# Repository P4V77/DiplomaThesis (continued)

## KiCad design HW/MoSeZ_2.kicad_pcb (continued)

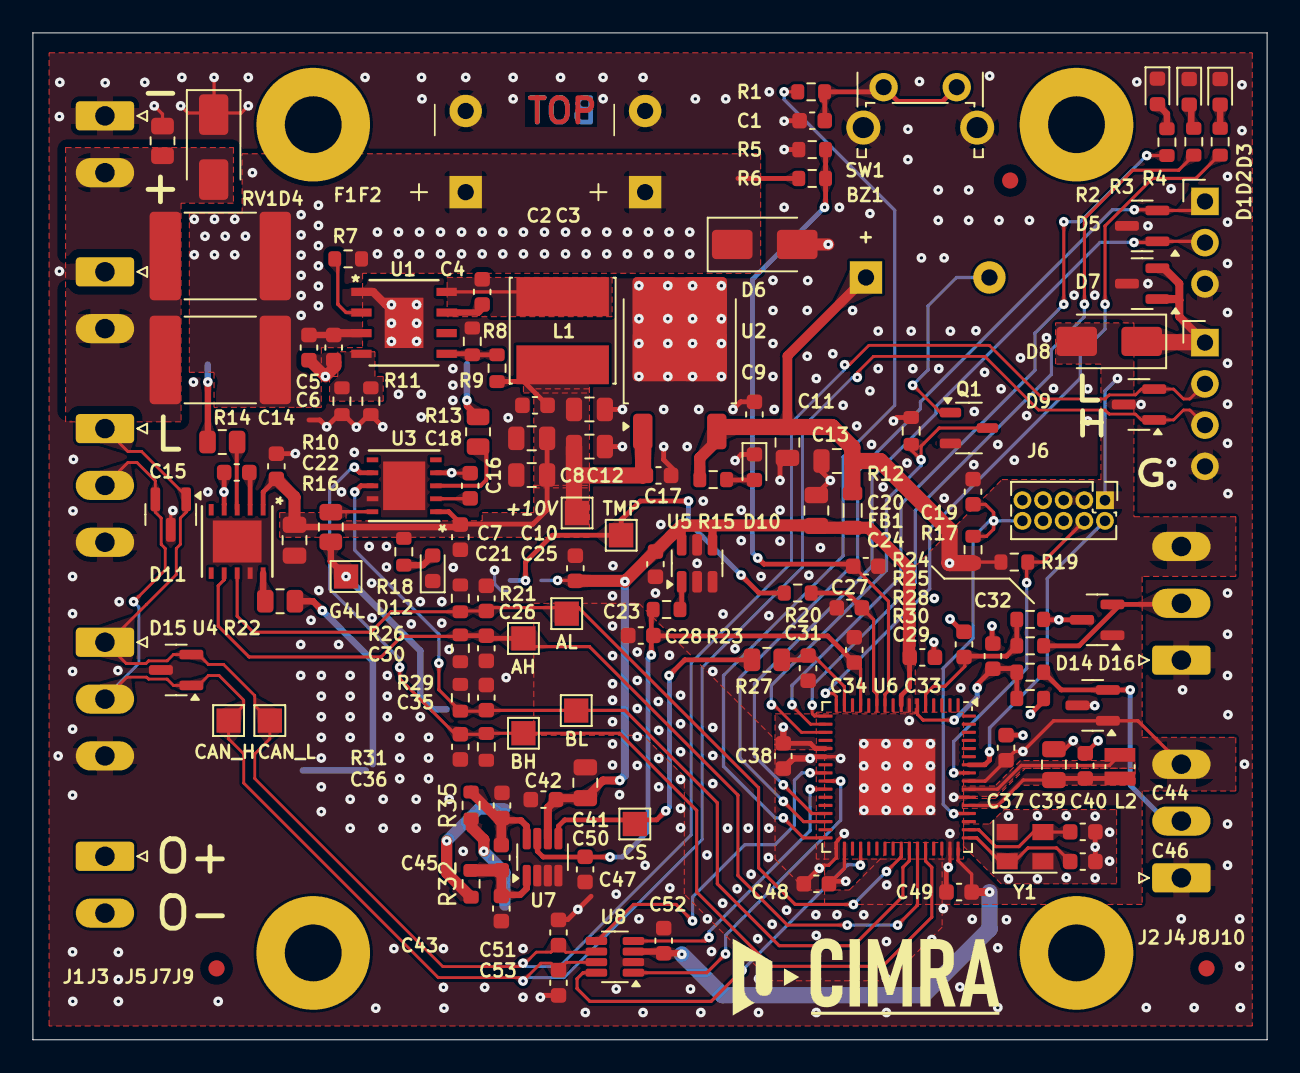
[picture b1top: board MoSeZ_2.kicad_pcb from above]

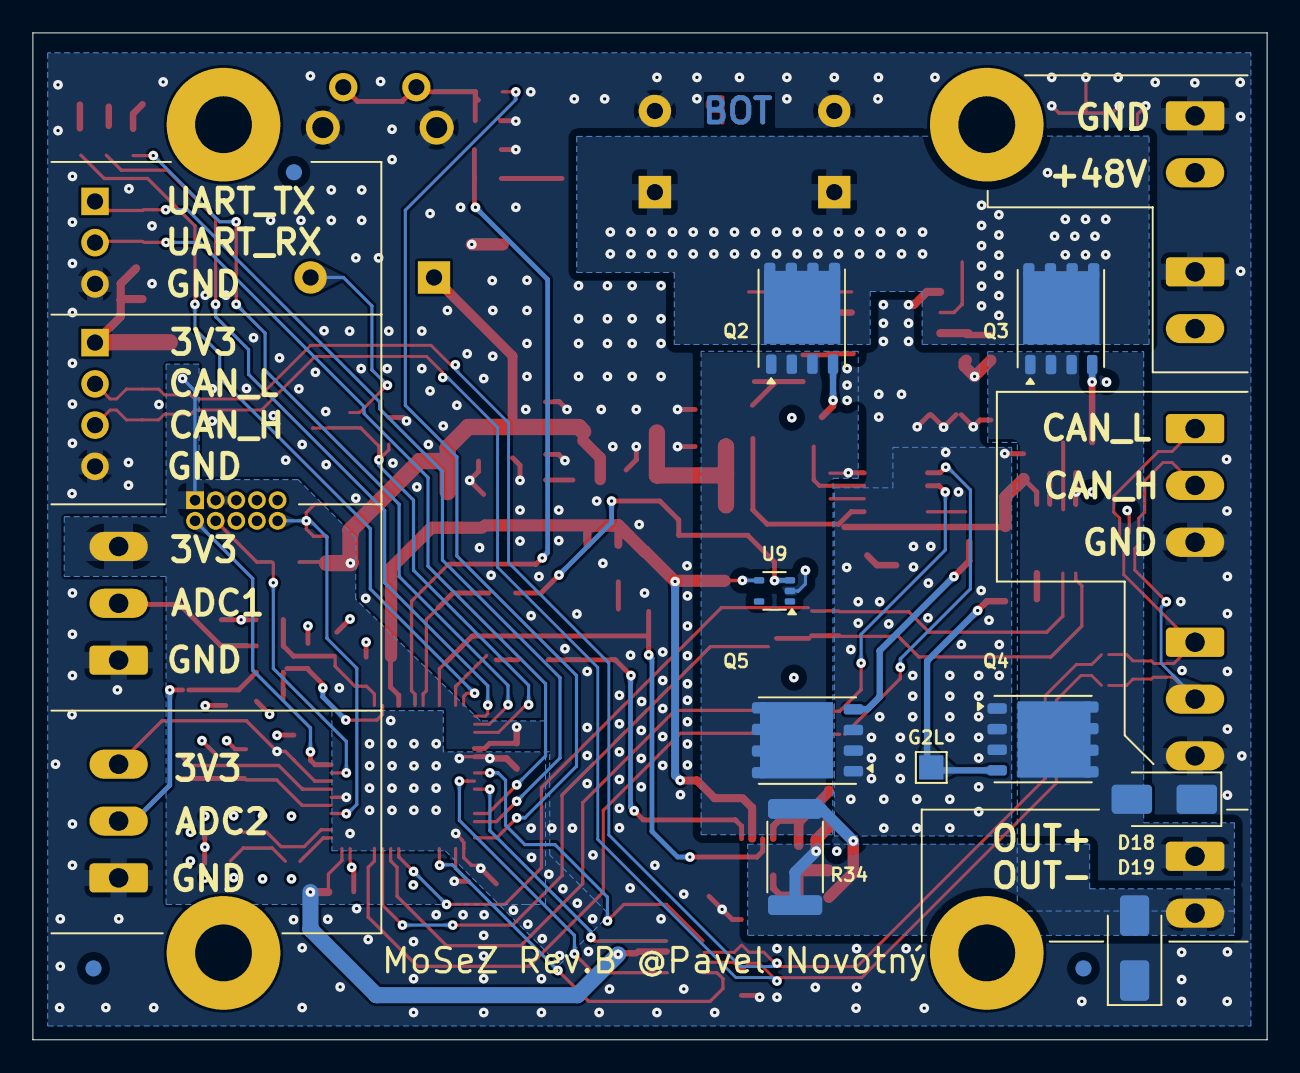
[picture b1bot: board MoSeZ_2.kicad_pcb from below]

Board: 4 copper layers, 76.0 x 62.0 mm, 160 parts (12 on the bottom side), 69 nets.

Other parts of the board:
G1: LOGO; cimra
G2: LOGO; zcu

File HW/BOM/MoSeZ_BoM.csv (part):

"Source:","/home/pavel/modular-current-source/HW_2.0/MoSeZ_2.kicad_sch"
"Date:","Thu 04 Apr 2024 10:45:10 AM CEST"
"Tool:","Eeschema 7.0.11-7.0.11~ubuntu22.04.1"
"Generator:","/usr/share/kicad/plugins/bom_csv_grouped_by_value.py"
"Component Count:","138"

"Collated Components:"

"Item","Qty","Reference(s)","Value","LibPart","Footprint","Datasheet","DNP","CENA","MNUMBER ","OBJCISLO","POZN","Sim.Device","Sim.Library","Sim.Name","Sim.Params","Sim.Pins","Vendor"
"1","1","BZ1","CMI1295IC0385(1285)","MiSPiZ-rescue:Buzzer-Device","Buzzer_Beeper:Buzzer_12x9.5RM7.6","https://cz.mouser.com/datasheet/2/670/cmi_1295ic_0385t-1776836.pdf","","24,33","CMI-1295IC-0385T ","490-CMI-1295IC-0385T ","","","","","","","https://cz.mouser.com/ProductDetail/CUI-Devices/CMI-1295IC-0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"
"2","23","C1, C4, C7, C9, C14, C17, C19, C21, C23, C24, C25, C27, C33, C37, C38, C40, C42, C43, C45, C48, C49, C50, C52","100nF/25V","Device:C_Small","Capacitor_SMD:C_0603_1608Metric","https://cz.mouser.com/datasheet/2/585/MLCC_Automotive-1837966.pdf","","2,23","CL10B104KA8WPNC ","187-CL10B104KA8WPNC","v cimře","","","","","","https://cz.mouser.com/ProductDetail/KEMET/C0603C104M3RACTU?q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"
"3","2","C2, C3","150uF","MiSPiZ-rescue:CP_Small-Device","Capacitor_THT:CP_Radial_D10.0mm_P5.00mm","https://cz.mouser.com/datasheet/2/315/Panasonic_08082018_Cap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","","18.31","EEU-FS1K151B","667-EEU-FS1K151B","","","","","","","https://cz.mouser.com/ProductDetail/Panasonic/EEU-FS1K151B?q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"
"4","7","C5, C6, C15, C18, C28, C31, C47","22nF/100V ","Device:C_Small","Capacitor_SMD:C_0603_1608Metric","https://cz.mouser.com/datasheet/2/447/KEM_C1002_X7R_SMD-3316098.pdf","","2,23","C0603C223K1RACTU","80-C0603C223K1R","","","","","","","https://cz.mouser.com/ProductDetail/KEMET/C0603C223K1RACTU?q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"
"5","7","C8, C10, C11, C12, C13, C20, C39","22uF/25V","Device:C_Small","Capacitor_SMD:C_0805_2012Metric","https://cz.mouser.com/datasheet/2/585/MLCC-1837944.pdf","","5,59","CL21A226MAYNNNE ","187-CL21A226MAYNNNE ","","","","","","","https://cz.mouser.com/ProductDetail/Samsung-Electro-Mechanic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"
"6","3","C16, C22, C41","2.2uF/25V","Device:C_Small","Capacitor_SMD:C_0805_2012Metric","https://cz.mouser.com/datasheet/2/585/MLCC-1837944.pdf","","2.69","CL21A225KAFNNNG ","187-CL21A225KAFNNNG ","","","","","","","https://cz.mouser.com/ProductDetail/Samsung-Electro-Mechanic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"
"7","6","C26, C30, C35, C36, C44, C46","18pF/10V","Device:C_Small","Capacitor_SMD:C_0603_1608Metric","https://cz.mouser.com/datasheet/2/447/UPY_NP0X5R_01005_4V_to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","","2,23","CC0603JRNP09BN180 ","603-CC603JRNPO9BN180 ","v cimře","","","","","","https://cz.mouser.com/ProductDetail/YAGEO/CC0603JRNP09BN180?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"
"8","4","C29, C32, C51, C53","1nF","Device:C_Small","Capacitor_SMD:C_0603_1608Metric","https://product.tdk.com/system/files/dam/doc/product/capacit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","","2,23","CGA3E2X7R2A102K080AA ","810-CGA3E2X7R2A102K ","","","","","","","https://cz.mouser.com/ProductDetail/TDK/CGA3E2X7R2A102K080AA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"
"9","1","D1","Green","Device:LED","Diode_SMD:D_0603_1608Metric","https://cz.mouser.com/datasheet/2/239/Lite-On-LTST-C190GKT-1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","","5,14","LTST-C190GKT","859-LTST-C190GKT","v cimře","","","","","","https://cz.mouser.com/ProductDetail/Lite-On/LTST-C190GKT?qs=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"
"10","1","D2","Red","Device:LED","Diode_SMD:D_0603_1608Metric","https://cz.mouser.com/datasheet/2/239/LTST_C190KRKT-1141828.pdf","","5,35","LTST-C190KRKT ","859-LTST-C190KRKT","v cimře","","","","","","https://cz.mouser.com/ProductDetail/Lite-On/LTST-C190KRKT?qs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"
"11","1","D3","Yellow","Device:LED","Diode_SMD:D_0603_1608Metric","https://cz.mouser.com/datasheet/2/239/Lite_On_LTST_C190YKT-3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","","5,81","LTST-C190YKT","859-LTST-C190YKT","v cimře","","","","","","https://cz.mouser.com/ProductDetail/Lite-On/LTST-C190YKT?qs=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"
"12","3","D4, D18, D19","SMAJ48CA","Diode:SMAJ48CA","Diode_SMD:D_SMA","https://cz.mouser.com/datasheet/2/447/SMAJ_1-1954892.pdf","","6.7","SMAJ48CA/TR13","603-SMAJ48CA/TR13","","","","","","","https://cz.mouser.com/ProductDetail/YAGEO/SMAJ48CA-TR13?qs=P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"
"13","7","D5, D7, D9, D11, D14, D15, D16","PESD3V3S2UT","Device:D_TVS_Dual_AAC","Package_TO_SOT_SMD:SOT-23","https://cz.mouser.com/datasheet/2/916/PESD3V3S2UT-3162503.pdf","","8.71","PESD3V3S2UT,215","771-PESD3V3S2UT-T/R","v cimře","","","","","","https://cz.mouser.com/ProductDetail/Nexperia/PESD3V3S2UT215?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"
"14","2","D6, D8","BYG10D ","Device:D","Diode_SMD:D_SMA","https://diotec.com/request/datasheet/byg10d.pdf","","3,58","BYG10D","637-BYG10D ","","D","","","","1=K 2=A","https://cz.mouser.com/ProductDetail/Diotec-Semiconductor/BYG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"
"15","2","D10, D12","Blue","Device:LED","Diode_SMD:D_0603_1608Metric","https://cz.mouser.com/datasheet/2/239/Lite-On-LTST-C193TBKT-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","","6,48","LTSTC193TBKT5A","859-LTSTC193TBKT5A","v cimře","","","","","","https://cz.mouser.com/ProductDetail/Lite-On/LTST-C193TBKT-5A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"
"16","2","F1, F2","2920L150/60MR","Device:Polyfuse_Small","Fuse:Fuse_2920_7451Metric","https://cz.mouser.com/datasheet/2/240/Littelfuse_10_27_2023_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","","19.2","2920L150/60MR","576-2920L150/60MR","","","","","","","https://cz.mouser.com/ProductDetail/Littelfuse/2920L150-60MR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"
"17","1","FB1","330R@100MHz","MiSPiZ-rescue:Ferrite_Bead_Small-Device","Inductor_SMD:L_0805_2012Metric","https://cz.mouser.com/datasheet/2/54/mgmumz-1067070.pdf","","2.23","MU2029-301Y","652-MU2029-301Y","v cimře","","","","","","https://cz.mouser.com/ProductDetail/Bourns/MU2029-301Y?qs=lr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"
"18","3","J1, J3, J9","3.5mm/2p","MiSPiZ-rescue:Conn_01x02_Female-Connector","Connector_Phoenix_MC:PhoenixContact_MC_1,5_2-G-3.5_1x02_P3.50mm_Horizontal","https://cz.mouser.com/datasheet/2/18/1/rLFHPy7mAQED-1379250.pdf","","8,71","OQ0212500000G","649-220107-C021A01LF ","v cimře","","","","","","https://cz.mouser.com/ProductDetail/Amphenol-Anytek/OQ021250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"
"19","1","J2","2.54mm/3p","MiSPiZ-rescue:Conn_01x03_Female-Connector","Connector_PinHeader_2.54mm:PinHeader_1x03_P2.54mm_Vertical","https://cdn.amphenol-cs.com/media/wysiwyg/files/documentatio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","","2.23","10129378-903001BLF","649-1012937890301BLF ","v cimře","","","","","","https://cz.mouser.com/ProductDetail/Amphenol-FCI/10129378-90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"
"20","1","J4","2.54/4p","MiSPiZ-rescue:Conn_01x04_Female-Connector","Connector_PinHeader_2.54mm:PinHeader_1x04_P2.54mm_Vertical","https://cdn.amphenol-cs.com/media/wysiwyg/files/documentatio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","","2.45","G800W304018EU ","523-G800W304018EU ","v cimře (7+4ks)","","","","","","https://cz.mouser.com/ProductDetail/Amphenol-Commercial-Prod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"
"21","4","J5, J7, J8, J10","3.5mm/3p","MiSPiZ-rescue:Conn_01x03_Female-Connector","Connector_Phoenix_MC:PhoenixContact_MC_1,5_3-G-3.5_1x03_P3.50mm_Horizontal","https://cz.mouser.com/datasheet/2/18/1/rLFHPy7mAQED-1379250.pdf","","10,94","OQ0312500000G ","649-220107-C031A01LF ","v cimře","","","","","","https://cz.mouser.com/ProductDetail/Amphenol-Anytek/OQ031250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"
"22","1","J6","PRG_Kon","Connector_Generic:Conn_02x05_Odd_Even","Connector_PinHeader_1.27mm:PinHeader_2x05_P1.27mm_Vertical","https://cdn.amphenol-cs.com/media/wysiwyg/files/documentatio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","","16,51","20021111-00010T4LF","649-221111-00010T4LF","","","","","","","https://cz.mouser.com/ProductDetail/Amphenol-FCI/20021111-00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"
"23","1","L1","47uH","Device:L","Inductor_SMD:L_Cenker_CKCS6045","https://cz.mouser.com/datasheet/2/54/SRN6045HA_datasheet-249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","","4.68","SRN6045HA-470M ","652-SRN6045HA-470M ","","","","","","","https://cz.mouser.com/ProductDetail/Bourns/SRN6045HA-470M?qs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"
"24","1","L2","10uH","Device:L_Small","Inductor_SMD:L_Wuerth_MAPI-2010","https://cz.mouser.com/datasheet/2/54/srn2010ta-1391479.pdf","","4.46","SRN2010TA-100M","652-SRN2010TA-100M","","","","","","","https://cz.mouser.com/ProductDetail/Bourns/SRN2010TA-100M?qs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"
"25","1","Q1","PJA3434_R1_00001","Device:Q_NMOS_DGS","Package_TO_SOT_SMD:SOT-23-3","https://cz.mouser.com/datasheet/2/115/DIOD_S_A0012994429_1-2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","","5,14","SSM3K16FV,L3F","621-DMN2310U-7 ","","","","","","","https://cz.mouser.com/ProductDetail/Diodes-Incorporated/DMN2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"
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
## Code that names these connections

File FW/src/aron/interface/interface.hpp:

#pragma once

#include <cstdint>
#include <array>
#include <string_view>
#include <sam.h>
#include <cctype>
#include <charconv>

#include "drivers/gpio/gpio_same5x.hpp"
#include "drivers/systick/systick.hpp"
#include "drivers/can/transcievers/tcan334.h"
#include "drivers/can/can_same5x.hpp"
#include "drivers/sam5x/gclk.hpp"
#include "drivers/sam5x/mclk.hpp"

#include "utils/logging/Logger.hpp"
#include "utils/logging/LoggerUart.hpp"
#include "utils/logging/LoggerCan.hpp"

#include "aron/communication/communication.hpp"

namespace aron
{

    using namespace nd;
    class Interface
    {
    public:
        /* LEDs */
        static inline drivers::Gpio_same5x led_green{drivers::gpio_pins::pa09};
        static inline drivers::Gpio_same5x led_yellow{drivers::gpio_pins::pa07};
        static inline drivers::Gpio_same5x led_red{drivers::gpio_pins::pa08};
        /* BUTTON */
        static inline drivers::Gpio_same5x button_1{drivers::gpio_pins::pa15, true};
        /* CAN */
        static inline drivers::TCAN334<drivers::Gpio_same5x> can_xcvr{drivers::gpio_pins::pa17, drivers::gpio_pins::pb11};
        static inline drivers::CAN_ATSAM_C_E can{CAN1, drivers::gpio_pins::pb13, drivers::gpio_pins::pb12};
        /* LOGGER */
        static inline nd::utils::LoggerUart logger{SERCOM4, drivers::gpio_pins::pa13, drivers::gpio_pins::pa12, 921'600, drivers::Gpio_alt_functions::D, 1, 0, 0};
        static inline nd::utils::LoggerCan can_logger; // Define the static member can_logger

        static void init_led();
        static void init_button();
        static void init_communication();
        static void init_can_logger();
        static void init_all();
        static void button_press();
    };
}

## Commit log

2025-12-04 Adding my Diploma Thesis repo
